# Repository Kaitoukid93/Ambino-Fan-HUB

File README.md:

# Ambino-Fan-HUB
A simple yet brilliant fan HUB that support dirt cheap coolmoon fan( an other Argb Fan)

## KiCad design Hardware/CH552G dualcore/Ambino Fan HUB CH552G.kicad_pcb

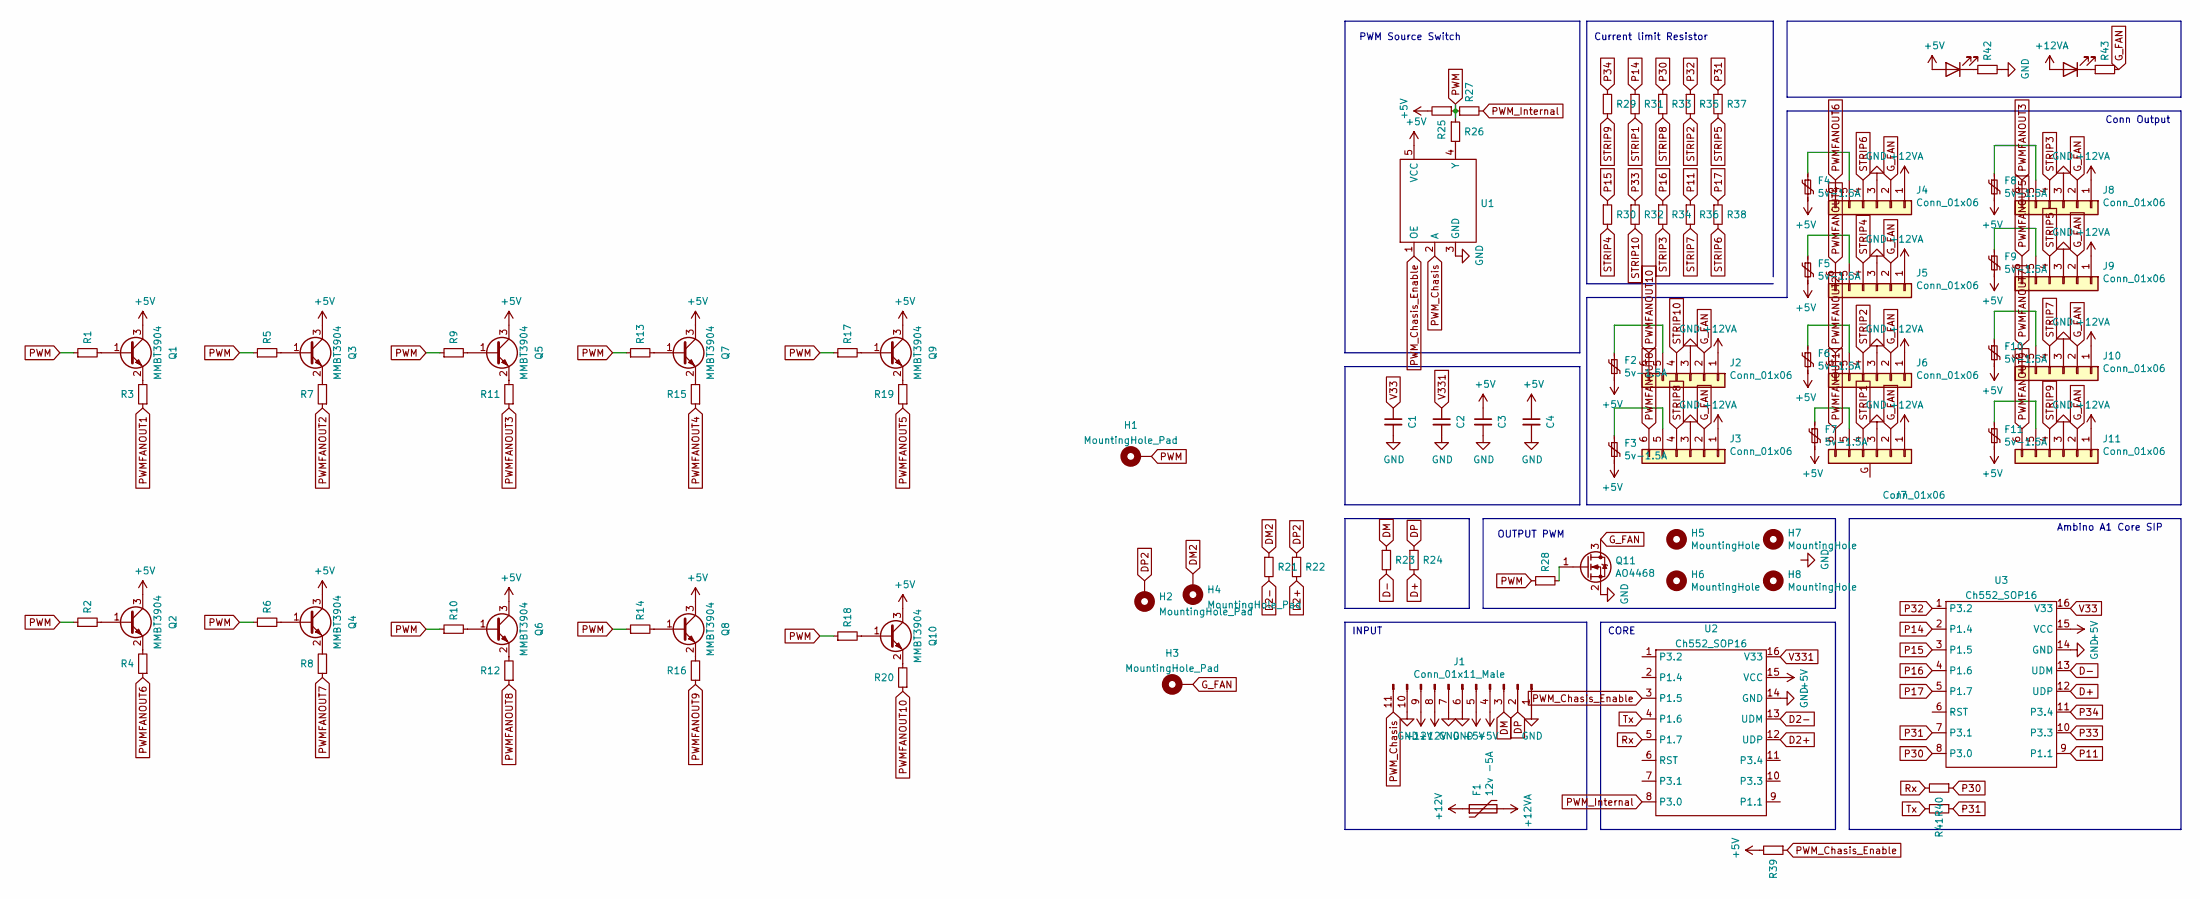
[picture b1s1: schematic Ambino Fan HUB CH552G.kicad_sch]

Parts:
C1, C2: 104; C_0603_1608Metric
C3, C4: 106; C_0603_1608Metric
D1: LED_BLUE; LED_0603_1608Metric
D2: LED_GREEN; LED_0603_1608Metric
F1: 12v -5A; Fuse_1206_3216Metric
F2, F3, F4, F5, F6, F7, F8, F9, F10, F11: 5v-1.5A; Fuse_0603_1608Metric
H1, H2, H3, H4: MountingHole_Pad; MountingHole_2.2mm_M2_DIN965_Pad
H5, H6, H7, H8: MountingHole; Mounting_Wuerth_WA-SMSI-M2_H1.5mm_9774015243
J1: Conn_01x11_Male; JST_PH_S11B-PH-SM4-TB_1x11-1MP_P2.00mm_Horizontal
J2, J3, J4, J5, J6, J7, J8, J9, J10, J11: Conn_01x06; JST_PH_B6B-PH-K_1x06_P2.00mm_Vertical
Q1, Q2, Q3, Q4, Q5, Q6, Q7, Q8, Q9, Q10: MMBT3904; SOT-23
Q11: AO4468; SOP-8_3.9x4.9mm_P1.27mm
R1, R2, R5, R6, R9, R10, R13, R14, R17, R18, R26, R27, R28: 150R; R_0603_1608Metric
R3, R4, R7, R8, R11, R12, R15, R16, R19, R20, R29, R30, R31, R32, R33, R34, R35, R36, R37, R38, R40, R41: 220R; R_0603_1608Metric
R21, R22, R23, R24: 33R; R_0603_1608Metric
R25, R39: 10k; R_0603_1608Metric
R42: 330R; R_0603_1608Metric
R43: 1K; R_0603_1608Metric
U1: SN74AHC1G125DBVR; SOT-23-5
U2, U3: Ch552_SOP16; SOP-16_3.9x9.9mm_P1.27mm

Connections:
+5V: C3.1, C4.1, D1.2 (A), F2.2, F3.2, F4.2, F5.2, F6.2, F7.2, F8.2, F9.2, F10.2, F11.2, J1.4, J1.5, Q1.3 (C), Q2.3 (C), Q3.3 (C), Q4.3 (C), Q5.3 (C), Q6.3 (C), Q7.3 (C), Q8.3 (C), Q9.3 (C), Q10.3 (C), R25.2, R39.2, U1.5 (VCC), U2.15 (VCC), U3.15 (VCC)
+12V: F1.1, J1.8, J1.9
+12VA: D2.2 (A), F1.2, J2.1, J3.1, J4.1, J5.1, J6.1, J7.1, J8.1, J9.1, J10.1, J11.1
D2+: R22.2, U2.12 (UDP)
D2-: R21.2, U2.13 (UDM)
D+: R24.2, U3.12 (UDP)
D-: R23.2, U3.13 (UDM)
DM: J1.3, R23.1
DM2: H4.1, R21.1; also elsewhere on the board
DP: J1.2, R24.1
DP2: H2.1, R22.1; also elsewhere on the board
GND: C1.2, C2.2, C3.2, C4.2, J1.1, J1.6, J1.7, J1.10, J2.3, J3.3, J4.3, J5.3, J6.3, J7.3, J8.3, J9.3, J10.3, J11.3, Q11.2 (S), R42.2, U1.3 (GND), U2.14 (GND), U3.14 (GND)
G_FAN: H3.1, J2.2, J3.2, J4.2, J5.2, J6.2, J7.2, J8.2, J9.2, J10.2, J11.2, Q11.3 (D), R43.2; also elsewhere on the board
unnamed: D1.1 (K), R42.1
unnamed: D2.1 (K), R43.1
unnamed: F2.1, J2.5
unnamed: F3.1, J3.5
unnamed: F4.1, J4.5
unnamed: F5.1, J5.5
unnamed: F6.1, J6.5
unnamed: F7.1, J7.5
unnamed: F8.1, J8.5
unnamed: F9.1, J9.5
unnamed: F10.1, J10.5
unnamed: F11.1, J11.5
unnamed: Q1.1 (B), R1.2
unnamed: Q1.2 (E), R3.2
unnamed: Q2.1 (B), R2.2
unnamed: Q2.2 (E), R4.2
unnamed: Q3.1 (B), R5.2
unnamed: Q3.2 (E), R7.2
unnamed: Q4.1 (B), R6.2
unnamed: Q4.2 (E), R8.2
unnamed: Q5.1 (B), R9.2
unnamed: Q5.2 (E), R11.2
unnamed: Q6.1 (B), R10.2
unnamed: Q6.2 (E), R12.2
unnamed: Q7.1 (B), R13.2
unnamed: Q7.2 (E), R15.2
unnamed: Q8.1 (B), R14.2
unnamed: Q8.2 (E), R16.2
unnamed: Q9.1 (B), R17.2
unnamed: Q9.2 (E), R19.2
unnamed: Q10.1 (B), R18.2
unnamed: Q10.2 (E), R20.2
unnamed: Q11.1 (G), R28.2
unnamed: R26.2, U1.4 (Y)
P11: R36.1, U3.9 (P1.1)
P14: R31.1, U3.2 (P1.4)
P15: R30.1, U3.3 (P1.5)
P16: R34.1, U3.4 (P1.6)
P17: R38.1, U3.5 (P1.7)
P30: R33.1, R40.1, U3.8 (P3.0)
P31: R37.1, R41.1, U3.7 (P3.1)
P32: R35.1, U3.1 (P3.2)
P33: R32.1, U3.10 (P3.3)
P34: R29.1, U3.11 (P3.4)
PWM: H1.1, R1.1, R2.1, R5.1, R6.1, R9.1, R10.1, R13.1, R14.1, R17.1, R18.1, R25.1, R26.1, R27.1, R28.1; also elsewhere on the board
PWMFANOUT1: J7.6, R3.1
PWMFANOUT2: J6.6, R7.1
PWMFANOUT3: J8.6, R11.1
PWMFANOUT4: J5.6, R15.1
PWMFANOUT5: J9.6, R19.1
PWMFANOUT6: J4.6, R4.1
PWMFANOUT7: J10.6, R8.1
PWMFANOUT8: J3.6, R12.1
PWMFANOUT9: J11.6, R16.1
PWMFANOUT10: J2.6, R20.1
PWM_Chasis: J1.11, U1.2 (A)
PWM_Chasis_Enable: R39.1, U1.1 (OE), U2.3 (P1.5)
PWM_Internal: R27.2, U2.8 (P3.0)
Rx: R40.2, U2.5 (P1.7)
STRIP1: J7.4, R31.2
STRIP2: J6.4, R35.2
STRIP3: J8.4, R34.2
STRIP4: J5.4, R30.2
STRIP5: J9.4, R37.2
STRIP6: J4.4, R38.2
STRIP7: J10.4, R36.2
STRIP8: J3.4, R33.2
STRIP9: J11.4, R29.2
STRIP10: J2.4, R32.2
Tx: R41.2, U2.4 (P1.6)
V33: C1.1, U3.16 (V33)
V331: C2.1, U2.16 (V33)

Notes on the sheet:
Conn Output
Ambino A1 Core SIP
OUTPUT PWM
Current limit Resistor
CORE
INPUT
PWM Source Switch

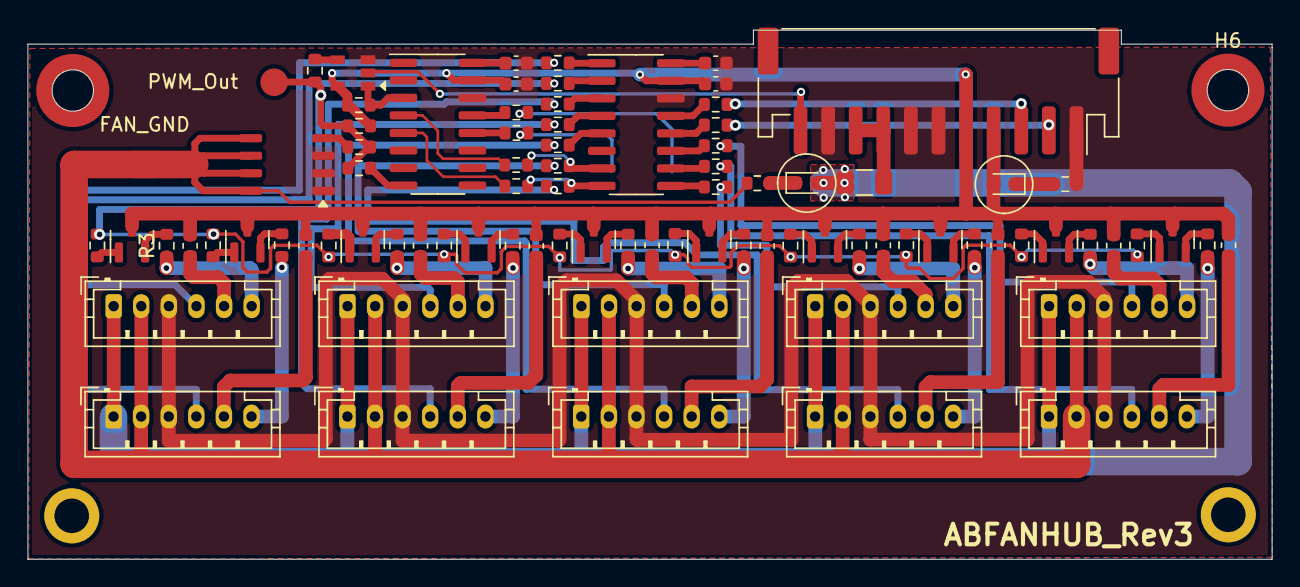
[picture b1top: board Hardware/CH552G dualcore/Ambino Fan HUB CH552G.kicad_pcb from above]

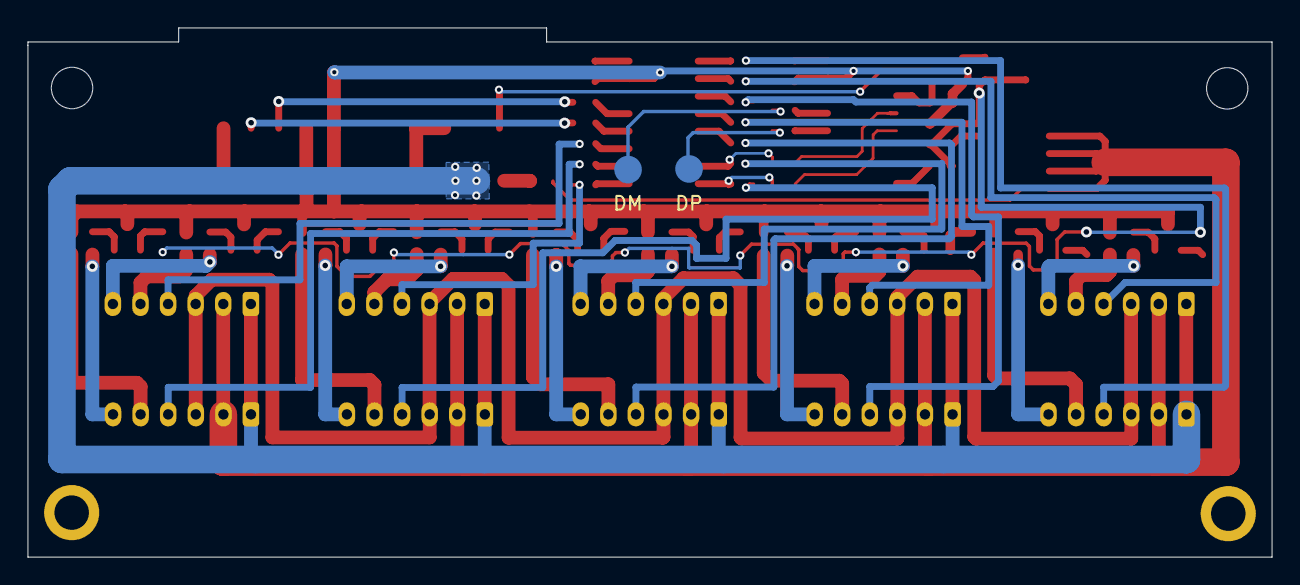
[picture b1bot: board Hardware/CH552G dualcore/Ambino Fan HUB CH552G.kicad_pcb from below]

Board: 2 copper layers, 90.2 x 38.4 mm, 93 parts (2 on the bottom side), 85 nets.

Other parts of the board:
DM: MountingHole_Pad; MountingHole_2.2mm_M2_DIN965_Pad
DP: MountingHole_Pad; MountingHole_2.2mm_M2_DIN965_Pad
FAN_GND: MountingHole_Pad; MountingHole_2.2mm_M2_DIN965_Pad
PWM_Out: MountingHole_Pad; MountingHole_2.2mm_M2_DIN965_Pad

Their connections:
DM2: DM.1; also elsewhere on the board
DP2: DP.1; also elsewhere on the board
G_FAN: FAN_GND.1; also elsewhere on the board
PWM: PWM_Out.1; also elsewhere on the board

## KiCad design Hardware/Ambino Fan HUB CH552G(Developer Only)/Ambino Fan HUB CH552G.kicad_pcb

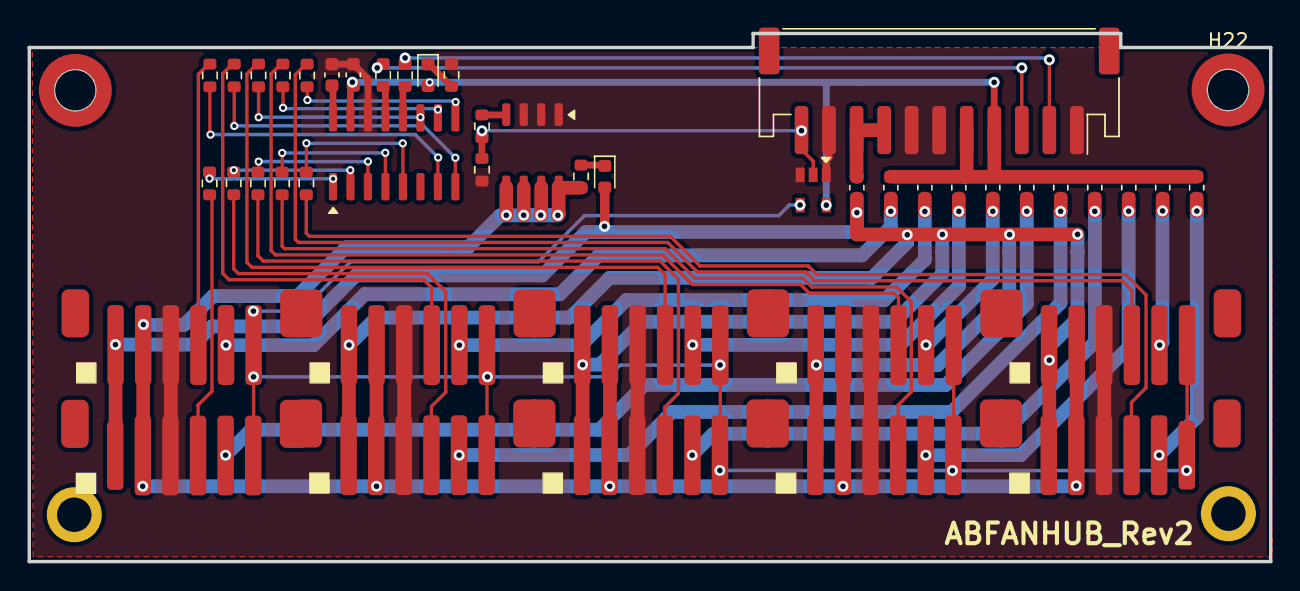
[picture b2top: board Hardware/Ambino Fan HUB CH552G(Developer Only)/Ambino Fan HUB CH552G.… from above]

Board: 2 copper layers, 90.2 x 38.4 mm, 49 parts (0 on the bottom side), 45 nets.

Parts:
C6: 104; C_0603_1608Metric
C7: 106; C_0603_1608Metric
D3: LED_BLUE; LED_0603_1608Metric
D4: LED_GREEN; LED_0603_1608Metric
F1, F2, F3, F4, F5, F6, F7, F8, F9, F10: 5v-1.5A; Fuse_0603_1608Metric
F11: 12v -5A; Fuse_0603_1608Metric
H21, H22, H23, H24: MountingHole; Mounting_Wuerth_WA-SMSI-M2_H1.5mm_9774015243
J1: https://item.taobao.com/item.htm?spm=a230r.1.14.2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; JST_PH_S11B-PH-SM4-TB_1x11-1MP_P2.00mm_Horizontal
J5, J6, J7, J8, J9, J10, J11, J12, J13, J14: Conn_01x06; JST_PH_B6B-PH-K_1x06_P2.00mm_Vertical
Q1: AO4468; SOP-8_3.9x4.9mm_P1.27mm
R1, R17, R18: 33R; R_0603_1608Metric
R2: 10K; R_0603_1608Metric
R7, R8, R9, R10, R11, R12, R13, R14, R15, R16: 220R; R_0603_1608Metric
R20: 330R; R_0603_1608Metric
R21: 1K; R_0603_1608Metric
U1: Ch552_SOP16; SOP-16_3.9x9.9mm_P1.27mm
U2: SN74AHC1G125DBVR; SOT-23-5

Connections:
+5V: C7.1, D3.2 (A), F1.2, F2.2, F3.2, F4.2, F5.2, F6.2, F7.2, F8.2, F9.2, F10.2, J1.4, J1.5, U1.15 (VCC), U2.5 (Y)
+12V: F11.1, J1.8, J1.9
+12VA: D4.2 (A), F11.2, J5.1, J6.1, J7.1, J8.1, J9.1, J10.1, J11.1, J12.1, J13.1, J14.1
D+: R18.2, U1.12 (UDP)
D-: R17.2, U1.13 (UDM)
DM: J1.3, R17.1
DP: J1.2, R18.1
GND: C6.2, C7.2, J1.1, J1.6, J1.7, J1.10, J5.3, J6.3, J7.3, J8.3, J9.3, J10.3, J11.3, J12.3, J13.3, J14.3, Q1.2 (S), R2.2, R20.2, U1.14 (GND), U2.1 (OE), U2.3 (GND)
G_FAN: J5.2, J6.2, J7.2, J8.2, J9.2, J10.2, J11.2, J12.2, J13.2, J14.2, Q1.3 (D), R21.2
unnamed: D3.1 (K), R20.1
unnamed: D4.1 (K), R21.1
unnamed: F1.1, J5.5
unnamed: F2.1, J6.5
unnamed: F3.1, J7.5
unnamed: F4.1, J8.5
unnamed: F5.1, J9.5
unnamed: F6.1, J10.5
unnamed: F7.1, J11.5
unnamed: F8.1, J12.5
unnamed: F9.1, J13.5
unnamed: F10.1, J14.5
P11: R14.1, U1.9 (P1.1)
P14: R9.1, U1.2 (P1.4)
P15: R8.1, U1.3 (P1.5)
P16: R12.1, U1.4 (P1.6)
P17: R16.1, U1.5 (P1.7)
P30: R11.1, U1.8 (P3.0)
P31: R15.1, U1.7 (P3.1)
P32: R13.1, U1.1 (P3.2)
P33: R10.1, U1.10 (P3.3)
P34: R7.1, U1.11 (P3.4)
PWM_Chasis: J1.11, R1.1, R2.1, U2.2 (A)
PWM_Chasis_OUT: J5.6, J6.6, J7.6, J8.6, J10.6, J11.6, J12.6, J13.6, J14.6, U2.4 (VCC)
PWM_Out: Q1.1 (G), R1.2
STRIP1: J10.4, R15.2
STRIP2: J9.4, R13.2
STRIP3: J11.4, R11.2
STRIP4: J8.4, R9.2
STRIP5: J12.4, R7.2
STRIP6: J7.4, R8.2
STRIP7: J13.4, R10.2
STRIP8: J6.4, R12.2
STRIP9: J14.4, R14.2
STRIP10: J5.4, R16.2
V33: C6.1, U1.16 (V33)

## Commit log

2021-12-05 Add firmware Add Unique ID as Serial Number
2021-12-08 change how data is sent and received on hub object support 1000 leds with only 1 kbyte of ram
2021-12-10 Hardware and firmware development init
2021-12-10 Add 3D files
2021-12-27 fix 74hc pin
2021-12-31 add support file and user manual
2022-01-03 update 3d file
2022-02-18 add packaging information
2022-02-22 fix pwm pin(wire and connector)
2022-05-16 update before manufacturing
2022-05-30 new firmware 1.0.1
2022-07-25 update dualcore
